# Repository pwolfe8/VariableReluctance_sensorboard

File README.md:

# VariableReluctance_sensorboard
This was my tutorial board that got me into "hardware"/board design.  My roommate was making an ECU for his Volvo 240 and needed a variable reluctance sensor board to detect the position and speed of the engine by monitoring a missing tooth gear on the crankshaft.  So he let me do this as a tutorial since it was simple enough and showed me the PCB design process.

Though my first PCB started with Eagle, I switched to KiCAD soon after (just like many people did since Autodesk acquired Eagle in June 2016).

___
Also did I mention I'm into memes?

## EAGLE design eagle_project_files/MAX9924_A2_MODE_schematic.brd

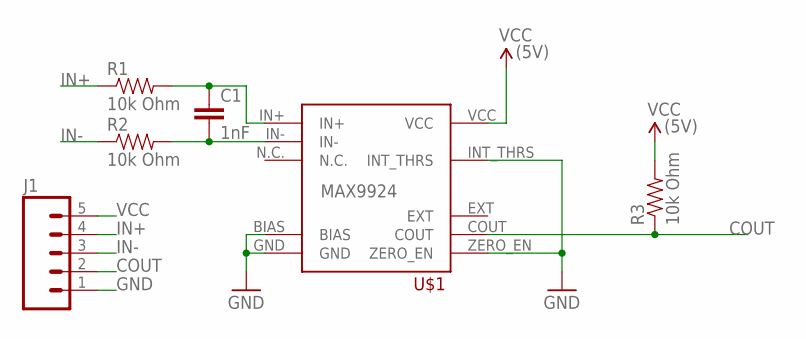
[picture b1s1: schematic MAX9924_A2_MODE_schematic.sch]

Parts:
C1: 1nF; CAP-PTH-SMALL
J1: M05PTH; 1X05
R1, R2, R3: 10k Ohm; AXIAL-0.4
U$1: MAX9924

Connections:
COUT: J1.2, R3.P$1 (1), U$1.COUT
GND: J1.1, U$1.BIAS, U$1.GND, U$1.INT_THRS, U$1.ZERO_EN
IN+: J1.4, R1.P$1 (1)
IN-: J1.3, R2.P$1 (1)
unnamed: C1.2, R2.P$2 (2), U$1.IN-
unnamed: C1.1, R1.P$2 (2), U$1.IN+
VCC: J1.5, R3.P$2 (2), U$1.VCC

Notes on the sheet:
(5V)

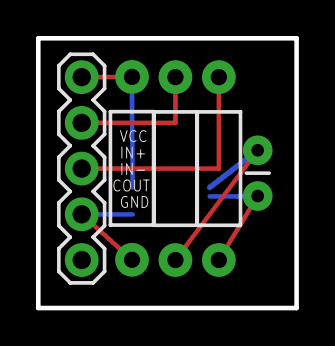
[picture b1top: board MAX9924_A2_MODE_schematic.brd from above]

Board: 2 copper layers, 14.4 x 15.0 mm, 6 parts (1 on the bottom side), 7 nets.

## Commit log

2018-01-30 added project files and readme/pics

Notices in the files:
parts and their libraries:
SparkFun-Capacitors: Licensing: Creative Commons ShareAlike 4.0 International - https://creativecommons.org/licenses/by-sa/4.0
